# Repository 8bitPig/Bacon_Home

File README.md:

# Bacon_Home
cc-by-nc-sa 4.0 / Teensy Based Midi USB to CV
should be compatible to teensy lc, teensy 3.1/3.2 and teensy 4! 
:)

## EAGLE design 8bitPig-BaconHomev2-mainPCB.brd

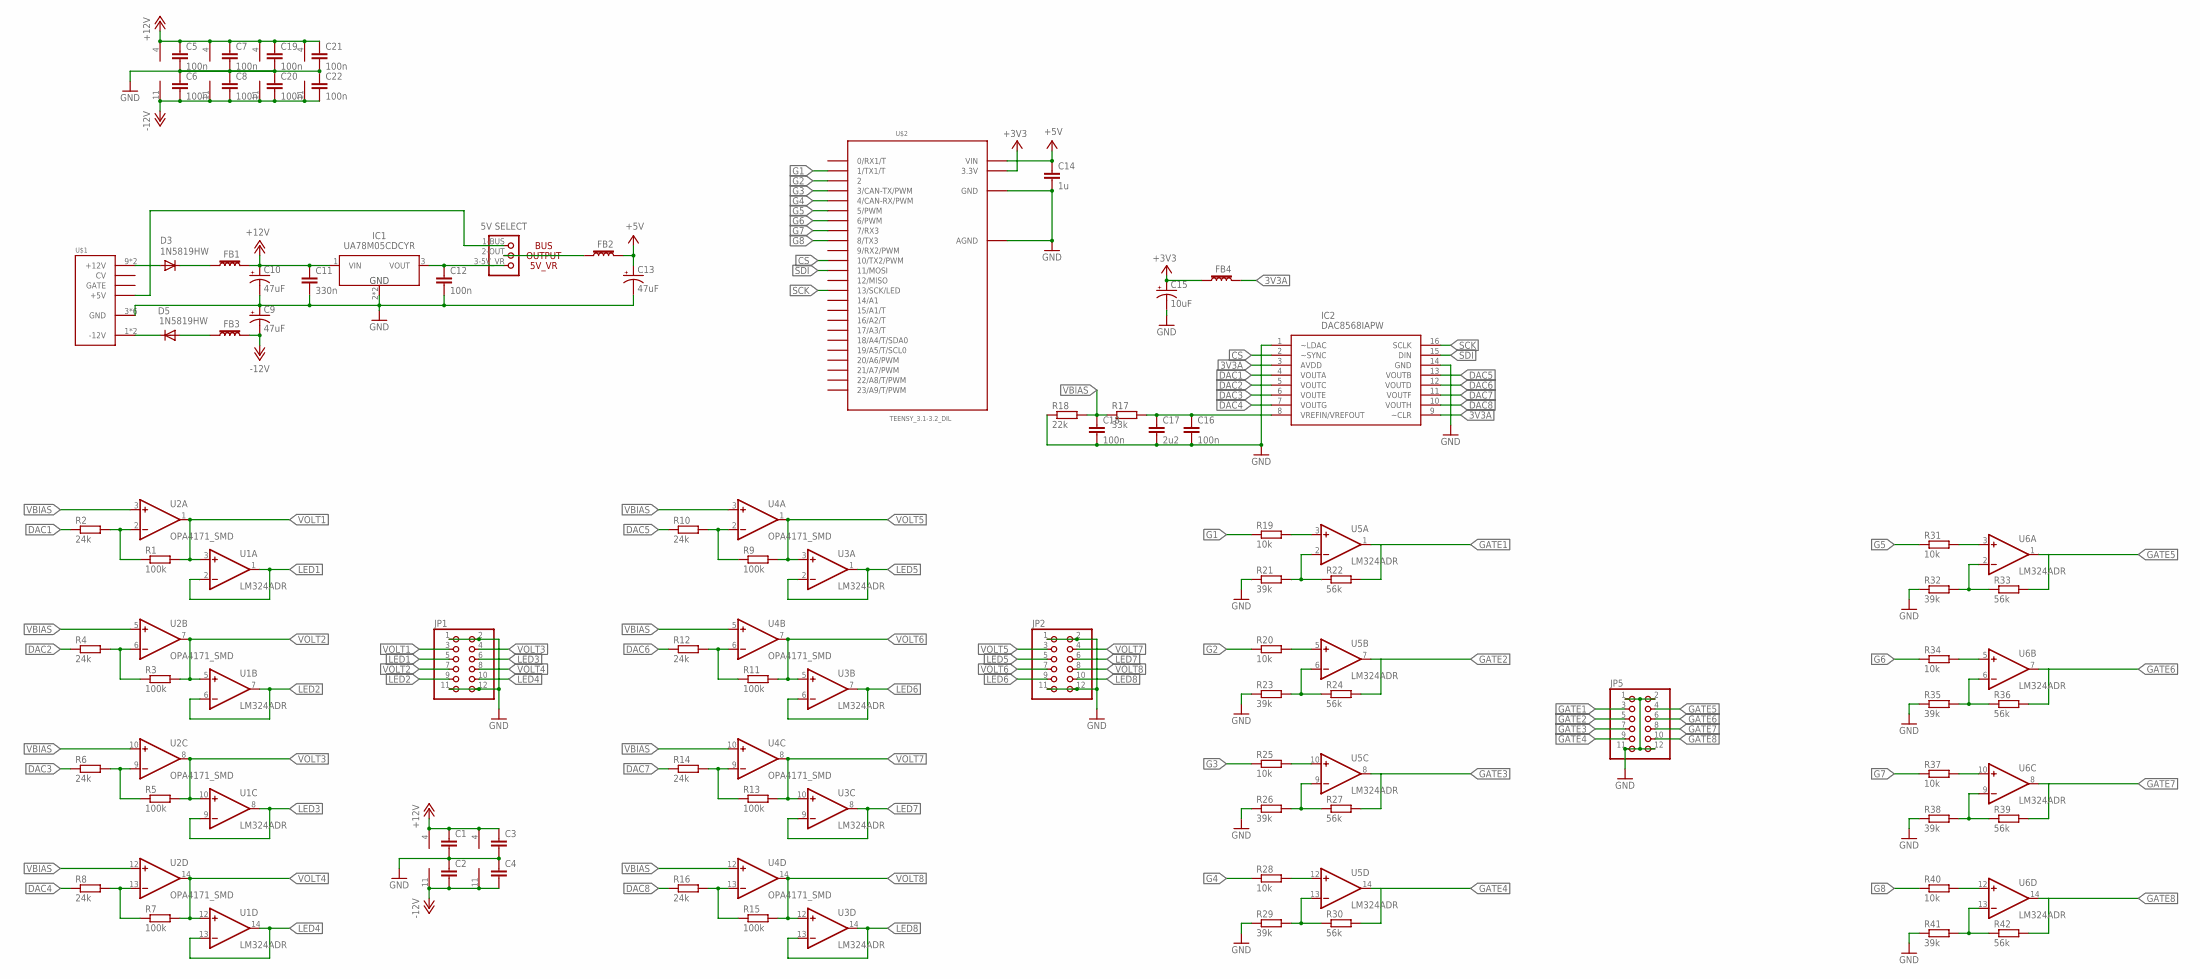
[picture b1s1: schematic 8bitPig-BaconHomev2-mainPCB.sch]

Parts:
C1, C2, C3, C4: C-EUC0603; C0603
C5, C6, C7, C8, C12, C16, C18, C19, C20, C21, C22: 100n; C0603
C9, C10, C13: 47uF; PANASONIC_D
C11: 330n; C0603
C14: 1u; C0603
C15: 10uF; PANASONIC_D
C17: 2u2; C0603
D3, D5: 1N5819HW; DIODE_SOD123
FB1, FB2, FB3, FB4: 30Ω/1.8A; 0603
IC1: UA78M05CDCYR; SOT230P700X180-4N
IC2: DAC8568IAPW; SOP65P640X120-16N
JP1, JP2, JP5: PINHD-2X6; 2X06
JP_5V: SELECTOR_POWER
R1, R3, R5, R7, R9, R11, R13, R15: 100k; R0603
R2, R4, R6, R8, R10, R12, R14, R16: 24k; R0603
R17: 33k; R0603
R18: 22k; R0603
R19, R20, R25, R28, R31, R34, R37, R40: 10k; R0603
R21, R23, R26, R29, R32, R35, R38, R41: 39k; R0603
R22, R24, R27, R30, R33, R36, R39, R42: 56k; R0603
U1, U3, U5, U6: LM324ADR; SO14
U2, U4: OPA4171_SMD; SO14
U$1: POWER; POWER_16
U$2: TEENSY_3.1-3.2_DIL; TEENSY_3.0-3.2&LC_DIL

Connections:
3V3A: FB4.2, IC2.3 (AVDD), IC2.9 (~CLR)
+3V3: C15.+, FB4.1, U$2.3.3V
+5V: C13.+, C14.1, FB2.2, U$2.VIN
+12V: C1.1, C3.1, C5.1, C7.1, C10.+, C11.1, C19.1, C21.1, FB1.2, IC1.1 (VIN), U1.4 (V+), U2.4 (V+), U3.4 (V+), U4.4 (V+), U5.4 (V+), U6.4 (V+)
-12V: C2.2, C4.2, C6.2, C8.2, C9.-, C20.2, C22.2, FB3.2, U1.11 (V-), U2.11 (V-), U3.11 (V-), U4.11 (V-), U5.11 (V-), U6.11 (V-)
CS: IC2.2 (~SYNC), U$2.10 (10/TX2/PWM)
DAC1: IC2.4 (VOUTA), R2.1
DAC2: IC2.5 (VOUTC), R4.1
DAC3: IC2.6 (VOUTE), R6.1
DAC4: IC2.7 (VOUTG), R8.1
DAC5: IC2.13 (VOUTB), R10.1
DAC6: IC2.12 (VOUTD), R12.1
DAC7: IC2.11 (VOUTF), R14.1
DAC8: IC2.10 (VOUTH), R16.1
G1: R19.1, U$2.1 (1/TX1/T)
G2: R20.1, U$2.2
G3: R25.1, U$2.3 (3/CAN-TX/PWM)
G4: R28.1, U$2.4 (4/CAN-RX/PWM)
G5: R31.1, U$2.5 (5/PWM)
G6: R34.1, U$2.6 (6/PWM)
G7: R37.1, U$2.7 (7/RX3)
G8: R40.1, U$2.8 (8/TX3)
GATE1: JP5.3, R22.2, U5.1 (OUT)
GATE2: JP5.5, R24.2, U5.7 (OUT)
GATE3: JP5.7, R27.2, U5.8 (OUT)
GATE4: JP5.9, R30.2, U5.14 (OUT)
GATE5: JP5.4, R33.2, U6.1 (OUT)
GATE6: JP5.6, R36.2, U6.7 (OUT)
GATE7: JP5.8, R39.2, U6.8 (OUT)
GATE8: JP5.10, R42.2, U6.14 (OUT)
GND: C1.2, C2.1, C3.2, C4.1, C5.2, C6.1, C7.2, C8.1, C9.+, C10.-, C11.2, C12.2, C13.-, C14.2, C15.-, C16.2, C17.2, C18.2, C19.2, C20.1, C21.2, C22.1, IC1.2 (GND), IC1.4 (GND), IC2.1 (~LDAC), IC2.14 (GND), JP1.1, JP1.2, JP1.11, JP1.12, JP2.1, JP2.2, JP2.11, JP2.12, JP5.1, JP5.2, JP5.11, JP5.12, R18.1, R21.1, R23.1, R26.1, R29.1, R32.1, R35.1, R38.1, R41.1, U$1.3 (GND), U$1.4 (GND), U$1.5 (GND), U$1.6 (GND), U$1.7 (GND), U$1.8 (GND), U$2.AGND, U$2.GND
LED1: JP1.5, U1.1 (OUT), U1.2 (-IN)
LED2: JP1.9, U1.6 (-IN), U1.7 (OUT)
LED3: JP1.6, U1.8 (OUT), U1.9 (-IN)
LED4: JP1.10, U1.13 (-IN), U1.14 (OUT)
LED5: JP2.5, U3.1 (OUT), U3.2 (-IN)
LED6: JP2.9, U3.6 (-IN), U3.7 (OUT)
LED7: JP2.6, U3.8 (OUT), U3.9 (-IN)
LED8: JP2.10, U3.13 (-IN), U3.14 (OUT)
unnamed: R1.1, R2.2, U2.2 (-IN)
unnamed: R3.1, R4.2, U2.6 (-IN)
unnamed: R5.1, R6.2, U2.9 (-IN)
unnamed: R7.1, R8.2, U2.13 (-IN)
unnamed: R9.1, R10.2, U4.2 (-IN)
unnamed: R11.1, R12.2, U4.6 (-IN)
unnamed: R13.1, R14.2, U4.9 (-IN)
unnamed: R15.1, R16.2, U4.13 (-IN)
unnamed: D3.A, U$1.9 (+12V), U$1.10 (+12V)
unnamed: D5.C, U$1.1 (-12V), U$1.2 (-12V)
unnamed: D5.A, FB3.1
unnamed: D3.C, FB1.1
unnamed: JP_5V.1-BUS, U$1.11 (+5V), U$1.12 (+5V)
unnamed: C12.1, IC1.3 (VOUT), JP_5V.3-5V_VR (3-VR)
unnamed: FB2.1, JP_5V.2-OUT
unnamed: C16.1, C17.1, IC2.8 (VREFIN/VREFOUT), R17.2
unnamed: R19.2, U5.3 (+IN)
unnamed: R20.2, U5.5 (+IN)
unnamed: R21.2, R22.1, U5.2 (-IN)
unnamed: R23.2, R24.1, U5.6 (-IN)
unnamed: R25.2, U5.10 (+IN)
unnamed: R26.2, R27.1, U5.9 (-IN)
unnamed: R28.2, U5.12 (+IN)
unnamed: R29.2, R30.1, U5.13 (-IN)
unnamed: R31.2, U6.3 (+IN)
unnamed: R32.2, R33.1, U6.2 (-IN)
unnamed: R34.2, U6.5 (+IN)
unnamed: R35.2, R36.1, U6.6 (-IN)
unnamed: R37.2, U6.10 (+IN)
unnamed: R38.2, R39.1, U6.9 (-IN)
unnamed: R40.2, U6.12 (+IN)
unnamed: R41.2, R42.1, U6.13 (-IN)
SCK: IC2.16 (SCLK), U$2.13 (13/SCK/LED)
SDI: IC2.15 (DIN), U$2.11 (11/MOSI)
VBIAS: C18.1, R17.1, R18.2, U2.3 (+IN), U2.5 (+IN), U2.10 (+IN), U2.12 (+IN), U4.3 (+IN), U4.5 (+IN), U4.10 (+IN), U4.12 (+IN)
VOLT1: JP1.3, R1.2, U1.3 (+IN), U2.1 (OUT)
VOLT2: JP1.7, R3.2, U1.5 (+IN), U2.7 (OUT)
VOLT3: JP1.4, R5.2, U1.10 (+IN), U2.8 (OUT)
VOLT4: JP1.8, R7.2, U1.12 (+IN), U2.14 (OUT)
VOLT5: JP2.3, R9.2, U3.3 (+IN), U4.1 (OUT)
VOLT6: JP2.7, R11.2, U3.5 (+IN), U4.7 (OUT)
VOLT7: JP2.4, R13.2, U3.10 (+IN), U4.8 (OUT)
VOLT8: JP2.8, R15.2, U3.12 (+IN), U4.14 (OUT)

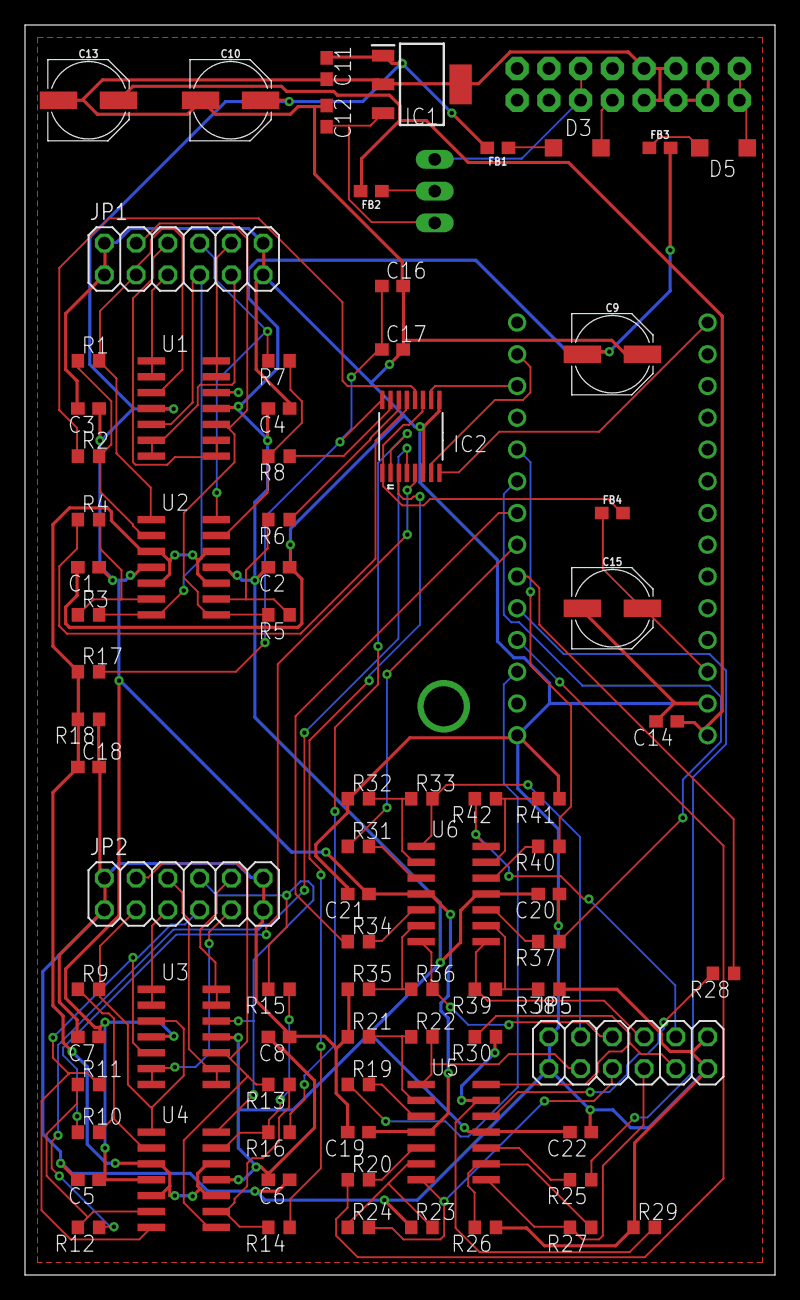
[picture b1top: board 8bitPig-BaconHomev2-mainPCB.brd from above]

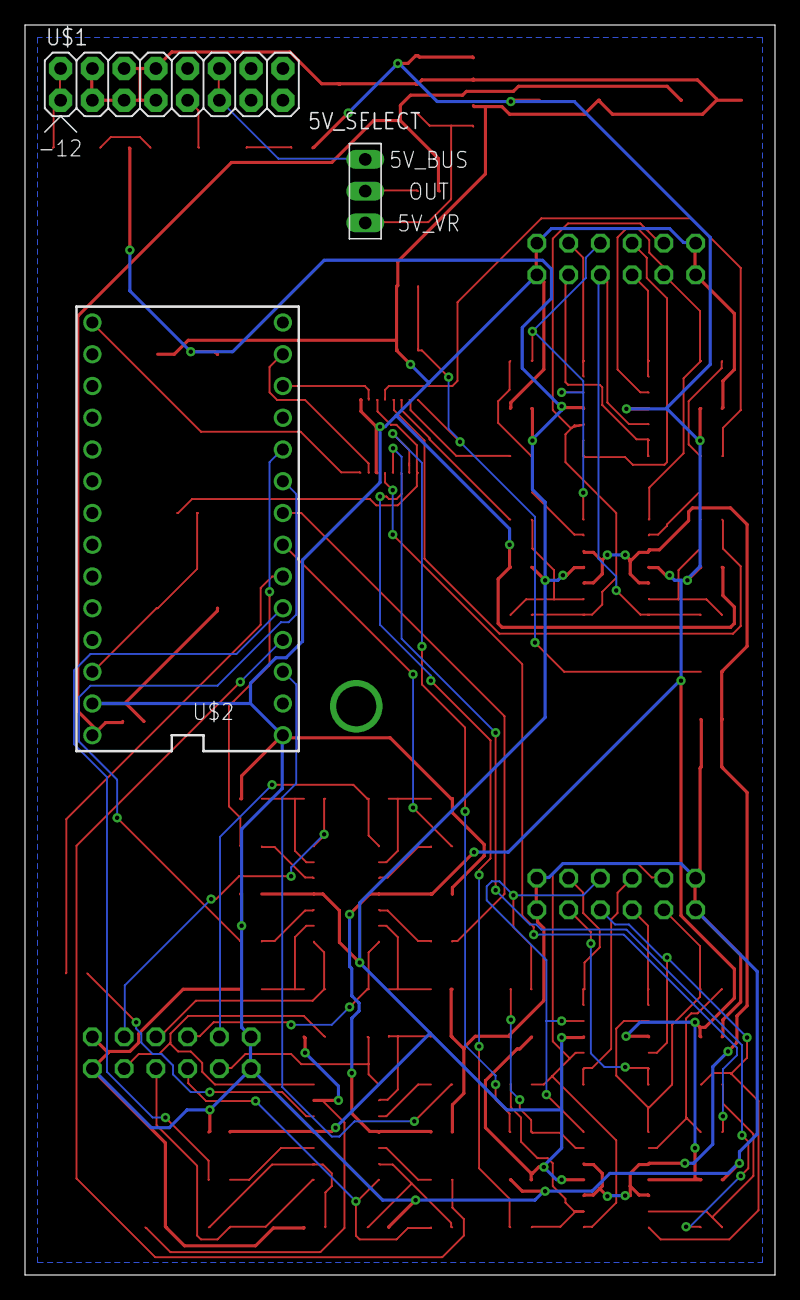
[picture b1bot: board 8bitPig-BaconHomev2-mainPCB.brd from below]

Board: 2 copper layers, 60.0 x 100.0 mm, 84 parts (3 on the bottom side), 82 nets.

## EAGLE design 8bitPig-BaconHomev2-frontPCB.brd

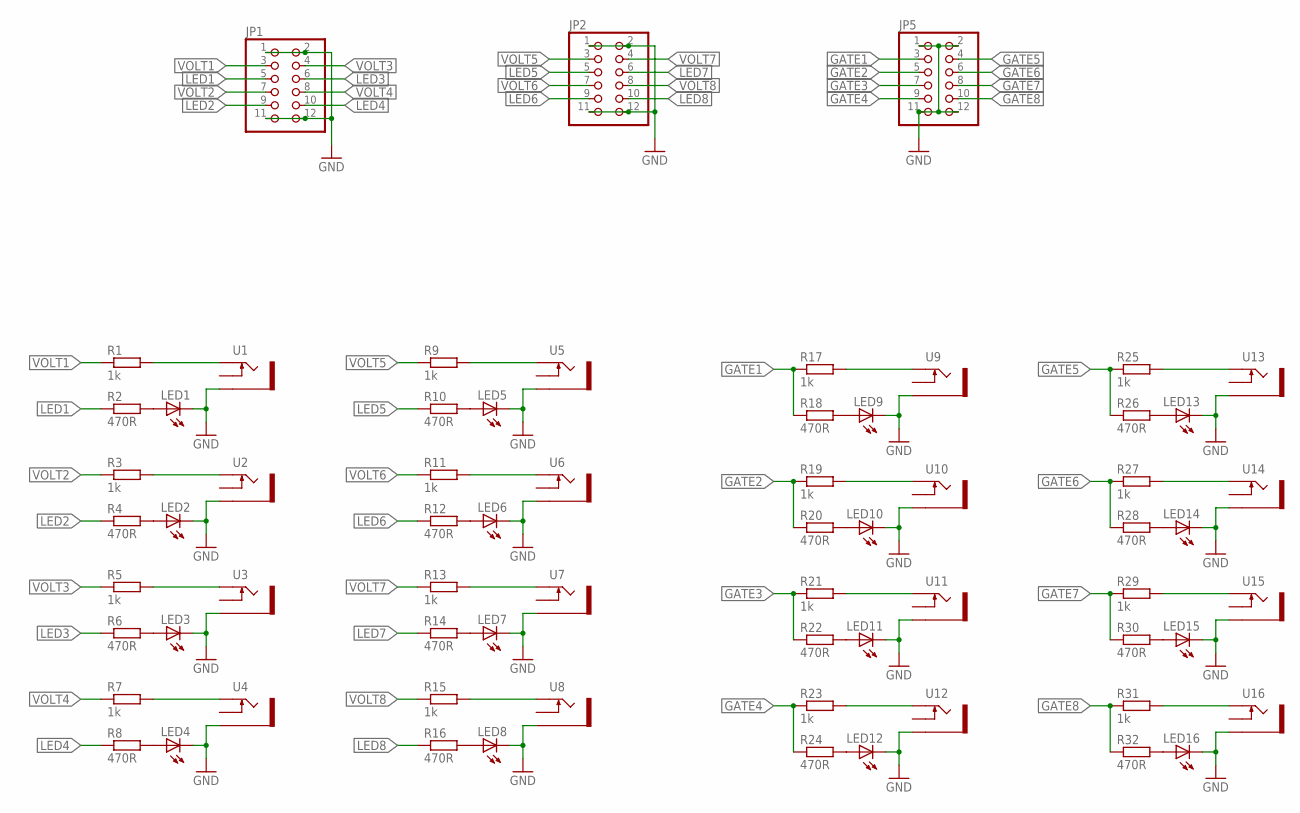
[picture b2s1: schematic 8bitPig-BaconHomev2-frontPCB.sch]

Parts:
JP1, JP2, JP5: PINHD-2X6; 2X06
LED1, LED2, LED3, LED4, LED5, LED6, LED7, LED8, LED9, LED10, LED11, LED12, LED13, LED14, LED15, LED16: LED3MM
R1, R3, R5, R7, R9, R11, R13, R15, R17, R19, R21, R23, R25, R27, R29, R31: 1k; R0603
R2, R4, R6, R8, R10, R12, R14, R16, R18, R20, R22, R24, R26, R28, R30, R32: 470R; R0603
U1, U2, U3, U4, U5, U6, U7, U8, U9, U10, U11, U12, U13, U14, U15, U16: THONKICONNNEW; WQP-PJ301M-12_JACK

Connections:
GATE1: JP5.3, R17.1, R18.1
GATE2: JP5.5, R19.1, R20.1
GATE3: JP5.7, R21.1, R22.1
GATE4: JP5.9, R23.1, R24.1
GATE5: JP5.4, R25.1, R26.1
GATE6: JP5.6, R27.1, R28.1
GATE7: JP5.8, R29.1, R30.1
GATE8: JP5.10, R31.1, R32.1
GND: JP1.1, JP1.2, JP1.11, JP1.12, JP2.1, JP2.2, JP2.11, JP2.12, JP5.1, JP5.2, JP5.11, JP5.12, LED1.K (C), LED2.K (C), LED3.K (C), LED4.K (C), LED5.K (C), LED6.K (C), LED7.K (C), LED8.K (C), LED9.K (C), LED10.K (C), LED11.K (C), LED12.K (C), LED13.K (C), LED14.K (C), LED15.K (C), LED16.K (C), U1.P$3_SLEEVE (SLEEVE), U2.P$3_SLEEVE (SLEEVE), U3.P$3_SLEEVE (SLEEVE), U4.P$3_SLEEVE (SLEEVE), U5.P$3_SLEEVE (SLEEVE), U6.P$3_SLEEVE (SLEEVE), U7.P$3_SLEEVE (SLEEVE), U8.P$3_SLEEVE (SLEEVE), U9.P$3_SLEEVE (SLEEVE), U10.P$3_SLEEVE (SLEEVE), U11.P$3_SLEEVE (SLEEVE), U12.P$3_SLEEVE (SLEEVE), U13.P$3_SLEEVE (SLEEVE), U14.P$3_SLEEVE (SLEEVE), U15.P$3_SLEEVE (SLEEVE), U16.P$3_SLEEVE (SLEEVE)
LED1: JP1.5, R2.1
LED2: JP1.9, R4.1
LED3: JP1.6, R6.1
LED4: JP1.10, R8.1
LED5: JP2.5, R10.1
LED6: JP2.9, R12.1
LED7: JP2.6, R14.1
LED8: JP2.10, R16.1
unnamed: LED1.A, R2.2
unnamed: R1.2, U1.P$1_TIP (TIP)
unnamed: LED2.A, R4.2
unnamed: R3.2, U2.P$1_TIP (TIP)
unnamed: LED3.A, R6.2
unnamed: R5.2, U3.P$1_TIP (TIP)
unnamed: LED4.A, R8.2
unnamed: R7.2, U4.P$1_TIP (TIP)
unnamed: LED5.A, R10.2
unnamed: R9.2, U5.P$1_TIP (TIP)
unnamed: LED6.A, R12.2
unnamed: R11.2, U6.P$1_TIP (TIP)
unnamed: LED7.A, R14.2
unnamed: R13.2, U7.P$1_TIP (TIP)
unnamed: LED8.A, R16.2
unnamed: R15.2, U8.P$1_TIP (TIP)
unnamed: LED9.A, R18.2
unnamed: R17.2, U9.P$1_TIP (TIP)
unnamed: LED10.A, R20.2
unnamed: R19.2, U10.P$1_TIP (TIP)
unnamed: LED11.A, R22.2
unnamed: R21.2, U11.P$1_TIP (TIP)
unnamed: LED12.A, R24.2
unnamed: R23.2, U12.P$1_TIP (TIP)
unnamed: LED13.A, R26.2
unnamed: R25.2, U13.P$1_TIP (TIP)
unnamed: LED14.A, R28.2
unnamed: R27.2, U14.P$1_TIP (TIP)
unnamed: LED15.A, R30.2
unnamed: R29.2, U15.P$1_TIP (TIP)
unnamed: LED16.A, R32.2
unnamed: R31.2, U16.P$1_TIP (TIP)
VOLT1: JP1.3, R1.1
VOLT2: JP1.7, R3.1
VOLT3: JP1.4, R5.1
VOLT4: JP1.8, R7.1
VOLT5: JP2.3, R9.1
VOLT6: JP2.7, R11.1
VOLT7: JP2.4, R13.1
VOLT8: JP2.8, R15.1

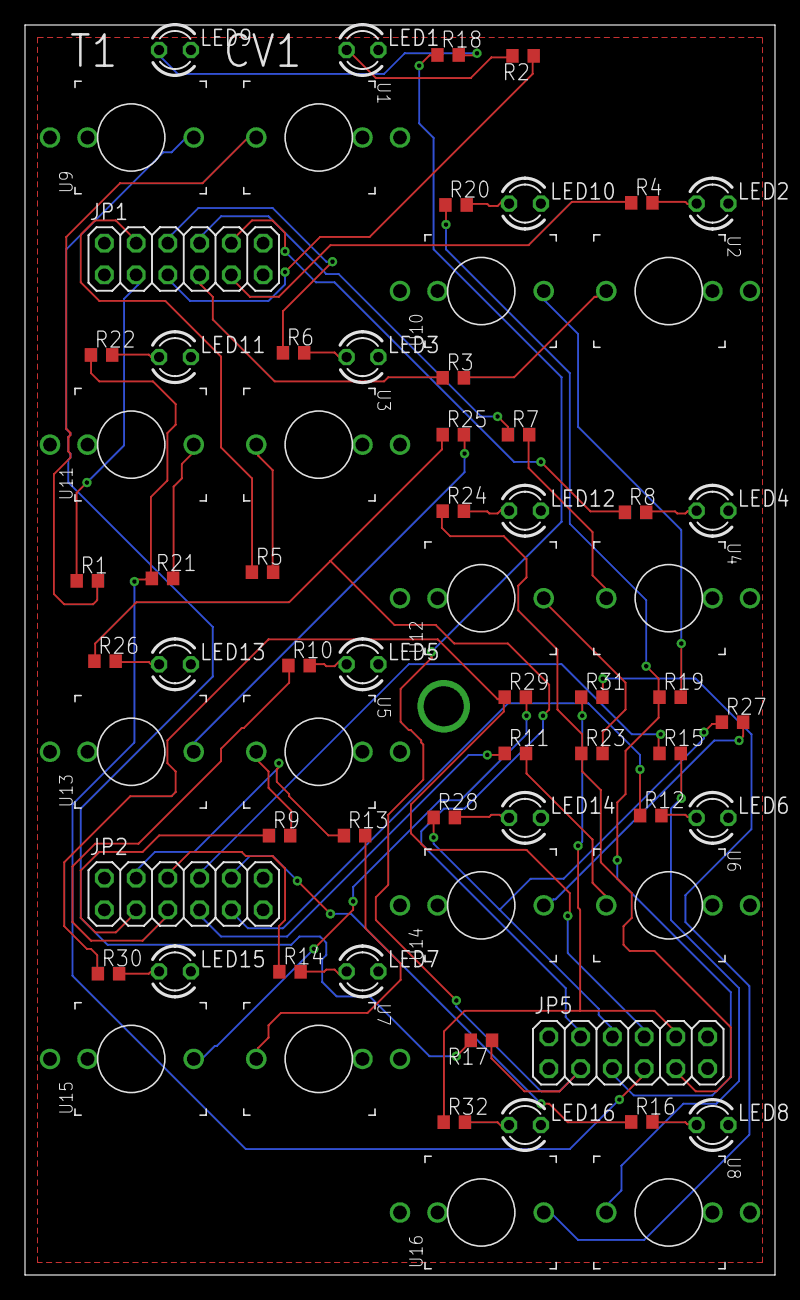
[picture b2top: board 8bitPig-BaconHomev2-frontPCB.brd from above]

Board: 2 copper layers, 60.0 x 100.0 mm, 67 parts (0 on the bottom side), 57 nets.

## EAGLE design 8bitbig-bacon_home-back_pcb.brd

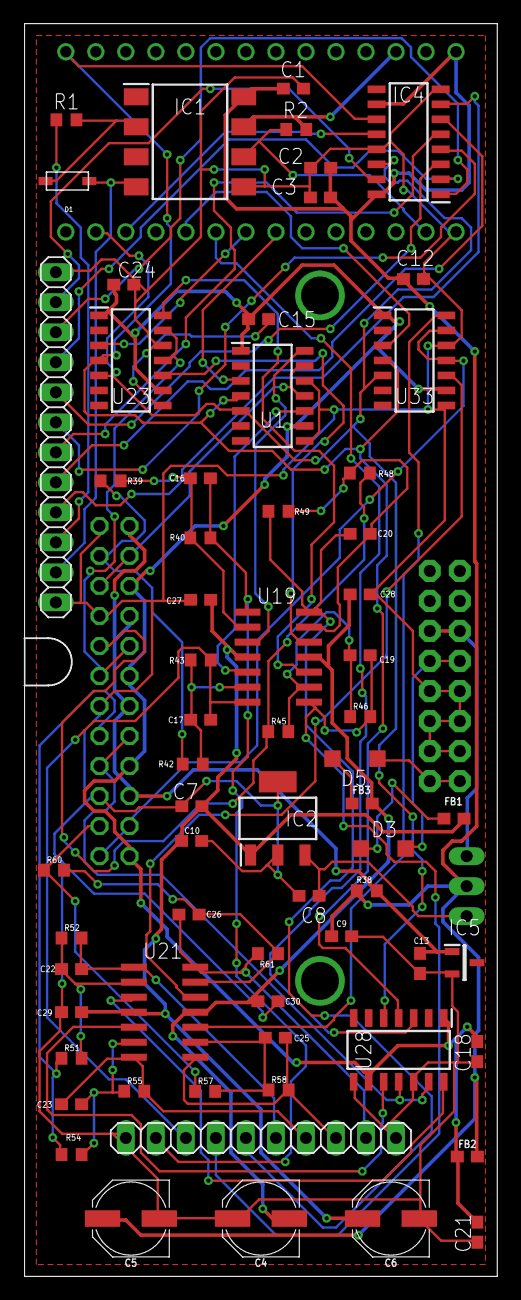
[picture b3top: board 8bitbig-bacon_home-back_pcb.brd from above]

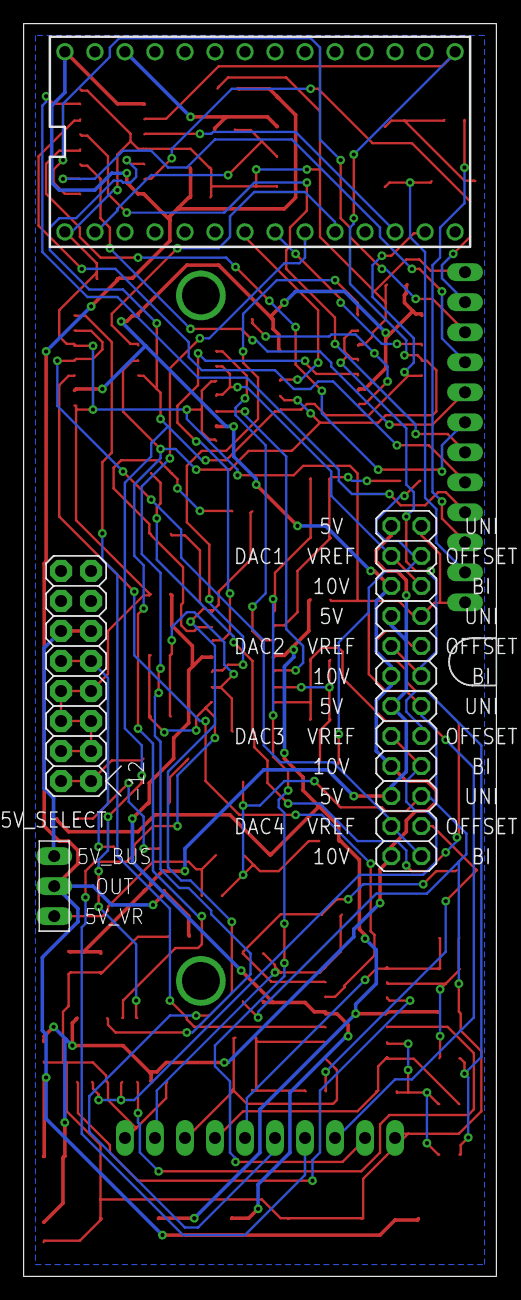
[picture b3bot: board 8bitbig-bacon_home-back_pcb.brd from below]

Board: 2 copper layers, 39.9 x 105.8 mm, 73 parts (7 on the bottom side), 64 nets.

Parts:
C1, C3, C8, C9, C10, C12, C13, C15, C18, C21, C24, C27, C28, C29, C30: 100n; C0603
C2: 1u; C0603
C4, C5, C6: 47uF; PANASONIC_D
C7: 330n; C0603
C16, C17, C19, C20, C22, C23, C25, C26: 47p; C0603
D1: 4148 SOD 123; SOD-123
D3, D5: 1N5819HW; DIODE_SOD123
DAC1, DAC2, DAC3, DAC4: NEW_SELECTOR
FB1, FB2, FB3: 30Ω/1.8A; 0603
IC1: 6N137S; SOP254P1016X460-8N
IC2: UA78M05CDCYR; SOT230P700X180-4N
IC4: SN74HC595DR; SOIC127P600X175-16N
IC5: LM4040CIM3-2.5_NOPB; SOT95P237X112-3N
JP1: SELECTOR_POWER
JP2: 1X12
JP3: 1X10
R1: 220R; R0603
R2, R38: 470R; R0603
R39, R40, R42, R43, R45, R46, R48, R49, R51, R52, R54, R55, R57, R58, R60, R61: 100k; R0603
TEENSY_3.2: TEENSY_3.1-3.2_DIL; TEENSY_3.0-3.2&LC_DIL
U1, U23, U28, U33: MCP4922T-E_SL; SOIC127P600X175-14N
U19, U21: TL074_SMD; SO14
U$1: PANEL_CABLE_CUTOUT
U$4: POWER; POWER_16

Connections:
5V_BUS: JP1.1-BUS, U$4.11, U$4.12
+2V5: C13.1, DAC1.6, DAC2.6, DAC3.6, DAC4.6, IC5.1, R38.2
+3V3: IC1.7, R2.2, TEENSY_3.2.3.3V
+5V: C1.1, C2.1, C3.1, C5.+, C9.1, C12.1, FB2.2, IC1.8, IC4.10, IC4.16, JP1.2-OUT, R38.1, TEENSY_3.2.VIN
+5V_A: C15.1, C18.1, C21.1, C24.1, DAC1.2, DAC2.2, DAC3.2, DAC4.2, FB2.1, U1.1, U1.9, U23.1, U23.9, U28.1, U28.9, U33.1, U33.9
+12V: C6.+, C7.1, C10.1, C27.1, C29.1, FB1.2, IC2.1, U19.4, U21.4
-12V: C4.-, C28.2, C30.2, FB3.2, U19.11, U21.11
CS1: TEENSY_3.2.5, U1.3
CS2: TEENSY_3.2.6, U23.3
CS3: TEENSY_3.2.7, U28.3
CS4: TEENSY_3.2.8, U33.3
CS6: IC4.12, TEENSY_3.2.10
CV1: C16.2, JP3.2, R40.2, U19.1
CV2: C17.2, JP3.3, R43.2, U19.7
CV3: C19.2, JP3.4, R46.2, U19.8
CV4: C20.2, JP3.5, R49.2, U19.14
CV5: C22.2, JP3.6, R52.2, U21.1
CV6: C23.2, JP3.7, R55.2, U21.7
CV7: C25.2, JP3.8, R58.2, U21.8
CV8: C26.2, JP3.9, R61.2, U21.14
DAC1: U1.14, U19.3
DAC2: U1.10, U19.5
DAC3: U19.10, U23.14
DAC4: U19.12, U23.10
DAC5: U21.3, U28.14
DAC6: U21.5, U28.10
DAC7: U21.10, U33.14
DAC8: U21.12, U33.10
GATE9: IC4.15, JP2.2
GATE10: IC4.1, JP2.3
GATE11: IC4.2, JP2.4
GATE12: IC4.3, JP2.5
GATE13: IC4.4, JP2.6
GATE14: IC4.5, JP2.7
GATE15: IC4.6, JP2.8
GATE16: IC4.7, JP2.9
GND: C1.2, C2.2, C3.2, C4.+, C5.-, C6.-, C7.2, C8.2, C9.2, C10.2, C12.2, C13.2, C15.2, C18.2, C21.2, C24.2, C27.2, C28.1, C29.2, C30.1, DAC1.5, DAC2.5, DAC3.5, DAC4.5, IC1.5, IC2.2, IC2.4, IC4.8, IC4.13, IC5.2, JP2.1, JP2.12, JP3.1, JP3.10, TEENSY_3.2.GND, U1.8, U1.12, U23.8, U23.12, U28.8, U28.12, U33.8, U33.12, U$4.3, U$4.4, U$4.5, U$4.6, U$4.7, U$4.8
MIDI_IN_L: D1.A, IC1.4, JP2.11
MIDI_IN_R: JP2.10, R1.1
unnamed: D1.C, IC1.2, R1.2
unnamed: IC1.6, R2.1, TEENSY_3.2.0
unnamed: D3.A, U$4.9, U$4.10
unnamed: D5.C, U$4.1, U$4.2
unnamed: D3.C, FB1.1
unnamed: C16.1, R39.2, R40.1, U19.2
unnamed: D5.A, FB3.1
unnamed: C8.1, IC2.3, JP1.3-5V_VR
unnamed: C17.1, R42.2, R43.1, U19.6
unnamed: C19.1, R45.2, R46.1, U19.9
unnamed: C20.1, R48.2, R49.1, U19.13
unnamed: C22.1, R51.2, R52.1, U21.2
unnamed: C23.1, R54.2, R55.1, U21.6
unnamed: C25.1, R57.2, R58.1, U21.9
unnamed: C26.1, R60.2, R61.1, U21.13
OFFSET1: DAC1.3, R39.1, R42.1
OFFSET2: DAC2.3, R45.1, R48.1
OFFSET3: DAC3.3, R51.1, R54.1
OFFSET4: DAC4.3, R57.1, R60.1
SCK: IC4.11, TEENSY_3.2.13, U1.4, U23.4, U28.4, U33.4
SDI: IC4.14, TEENSY_3.2.11, U1.5, U23.5, U28.5, U33.5
VREF1: DAC1.1, DAC1.4, U1.11, U1.13
VREF2: DAC2.1, DAC2.4, U23.11, U23.13
VREF3: DAC3.1, DAC3.4, U28.11, U28.13
VREF4: DAC4.1, DAC4.4, U33.11, U33.13

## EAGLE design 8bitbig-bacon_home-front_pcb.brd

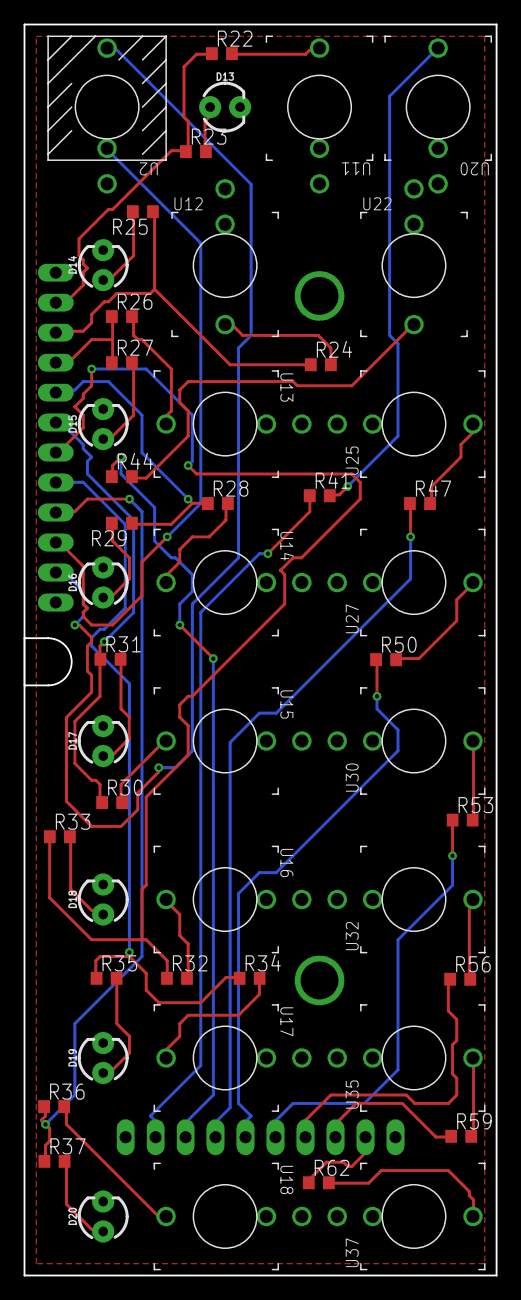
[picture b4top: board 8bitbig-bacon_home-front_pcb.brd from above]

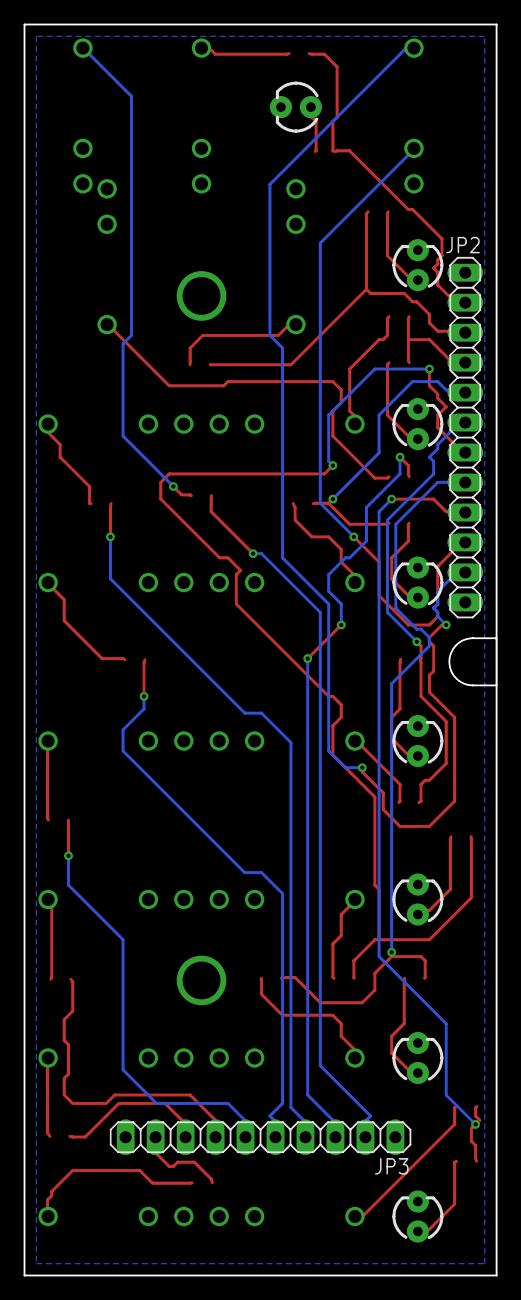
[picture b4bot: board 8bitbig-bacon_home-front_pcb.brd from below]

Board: 2 copper layers, 40.0 x 106.0 mm, 52 parts (2 on the bottom side), 43 nets.

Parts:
D13, D14, D15, D16, D17, D18, D19, D20: LED_3MM
JP2: 1X12
JP3: 1X10
R22, R23, R24, R25, R26, R27, R28, R29, R30, R31, R32, R33, R34, R35, R36, R37, R41, R44, R47, R50, R53, R56, R59, R62: 1k; R0603
U2: THONKI-STEREO; WQP-PJ366ST_JACK
U11, U12, U13, U14, U15, U16, U17, U18, U20, U22, U25, U27, U30, U32, U35, U37: THONKICONNNEW; WQP-PJ301M-12_JACK
U$1: PANEL_CABLE_CUTOUT

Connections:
CV1: JP3.2, R41.1
CV2: JP3.3, R44.1
CV3: JP3.4, R47.1
CV4: JP3.5, R50.1
CV5: JP3.6, R53.1
CV6: JP3.7, R56.1
CV7: JP3.8, R59.1
CV8: JP3.9, R62.1
GATE9: JP2.2, R22.1, R23.1
GATE10: JP2.3, R24.1, R25.1
GATE11: JP2.4, R26.1, R27.1
GATE12: JP2.5, R28.1, R29.1
GATE13: JP2.6, R30.1, R31.1
GATE14: JP2.7, R32.1, R33.1
GATE15: JP2.8, R34.1, R35.1
GATE16: JP2.9, R36.1, R37.1
GND: D13.K, D14.K, D15.K, D16.K, D17.K, D18.K, D19.K, D20.K, JP2.1, JP2.12, JP3.1, JP3.10, U11.P$3_SLEEVE, U12.P$3_SLEEVE, U13.P$3_SLEEVE, U14.P$3_SLEEVE, U15.P$3_SLEEVE, U16.P$3_SLEEVE, U17.P$3_SLEEVE, U18.P$3_SLEEVE, U20.P$3_SLEEVE, U22.P$3_SLEEVE, U25.P$3_SLEEVE, U27.P$3_SLEEVE, U30.P$3_SLEEVE, U32.P$3_SLEEVE, U35.P$3_SLEEVE, U37.P$3_SLEEVE
unnamed: JP2.11, U2.P$1_TIP
unnamed: JP2.10, U2.P$2_SWITCH
unnamed: R22.2, U11.P$1_TIP
unnamed: D13.A, R23.2
unnamed: R24.2, U12.P$1_TIP
unnamed: D14.A, R25.2
unnamed: R26.2, U13.P$1_TIP
unnamed: D15.A, R27.2
unnamed: R28.2, U14.P$1_TIP
unnamed: D16.A, R29.2
unnamed: R30.2, U15.P$1_TIP
unnamed: D17.A, R31.2
unnamed: R32.2, U16.P$1_TIP
unnamed: D18.A, R33.2
unnamed: R34.2, U17.P$1_TIP
unnamed: D19.A, R35.2
unnamed: R36.2, U18.P$1_TIP
unnamed: D20.A, R37.2
unnamed: R41.2, U20.P$1_TIP
unnamed: R44.2, U22.P$1_TIP
unnamed: R47.2, U25.P$1_TIP
unnamed: R50.2, U27.P$1_TIP
unnamed: R53.2, U30.P$1_TIP
unnamed: R56.2, U32.P$1_TIP
unnamed: R59.2, U35.P$1_TIP
unnamed: R62.2, U37.P$1_TIP

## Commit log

2019-08-19 Add files via upload
    updated correct part names & values. wired gates directly to GPIOs. used a better DAC and scaling for CV outs.
    CV Range -~5,2 to +5,25V
    Gates are scaled to 8V
    important parts are DAC8568A, OPA4171 and LM324

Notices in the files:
parts and their libraries:
SparkFun-Capacitors: Licensing: Creative Commons ShareAlike 4.0 International - https://creativecommons.org/licenses/by-sa/4.0
